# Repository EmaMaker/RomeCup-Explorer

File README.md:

# RomeCup Explorer

This repository contains the PCBs design files and code for the RomeCup Explorer playfield.

The RomeCup is a yearly event held by [Fondazione Mondo Digitale](https://mondodigitale.org) in
Rome, Italy, revolving around robotics and artificial intelligence. A big part of the event are the
robotics competitions aimed at middle and high school students. Some categories of competition are parallel to
the [RoboCup Junior](https://junior.robocup.org) (e.g. Soccer Open/LightWeight, Rescue Line), while
others are exclusive to RomeCup, like the Explorer category and, starting 2024, the Robotic Arms
category.

In the Explorer category, robots build and programmed by the students have to navigate a maze while
finding and recognizing different "hotspots". The hotspots can be of different kinds (in ascending
	order of points earned):

- Gas sources (1)
- Light source (2)
- Sound sources (3)

In 2024, we decided to rebuild the explorer category playfield from the ground up, favouring ease of
transport and assembly once on site (RomeCup is held every year at a different location, with the
	finals taking place in Rome Capitol every year).

To follow this route, we decided to have each hotspot have its own PCB to generate light and sound,
   instead of having a single source with cables running underneath the playfield. This also makes
   rearranging the maze easier in between rounds. In this repo, you can find the KiCad project files
   for the light and sound generation PCB, along side the BOM and manufacturing files for both
   standalone boards and panels, and the Arduino code powering the AtTiny412 microcontroller used in
   the sound boards. 

If you want to know more about the thought process and design decisions for the playfield, or about
the RoboCup 2024 event in general, I have written a [blog post](https://emamaker.com/events/romecup2024)
about it.

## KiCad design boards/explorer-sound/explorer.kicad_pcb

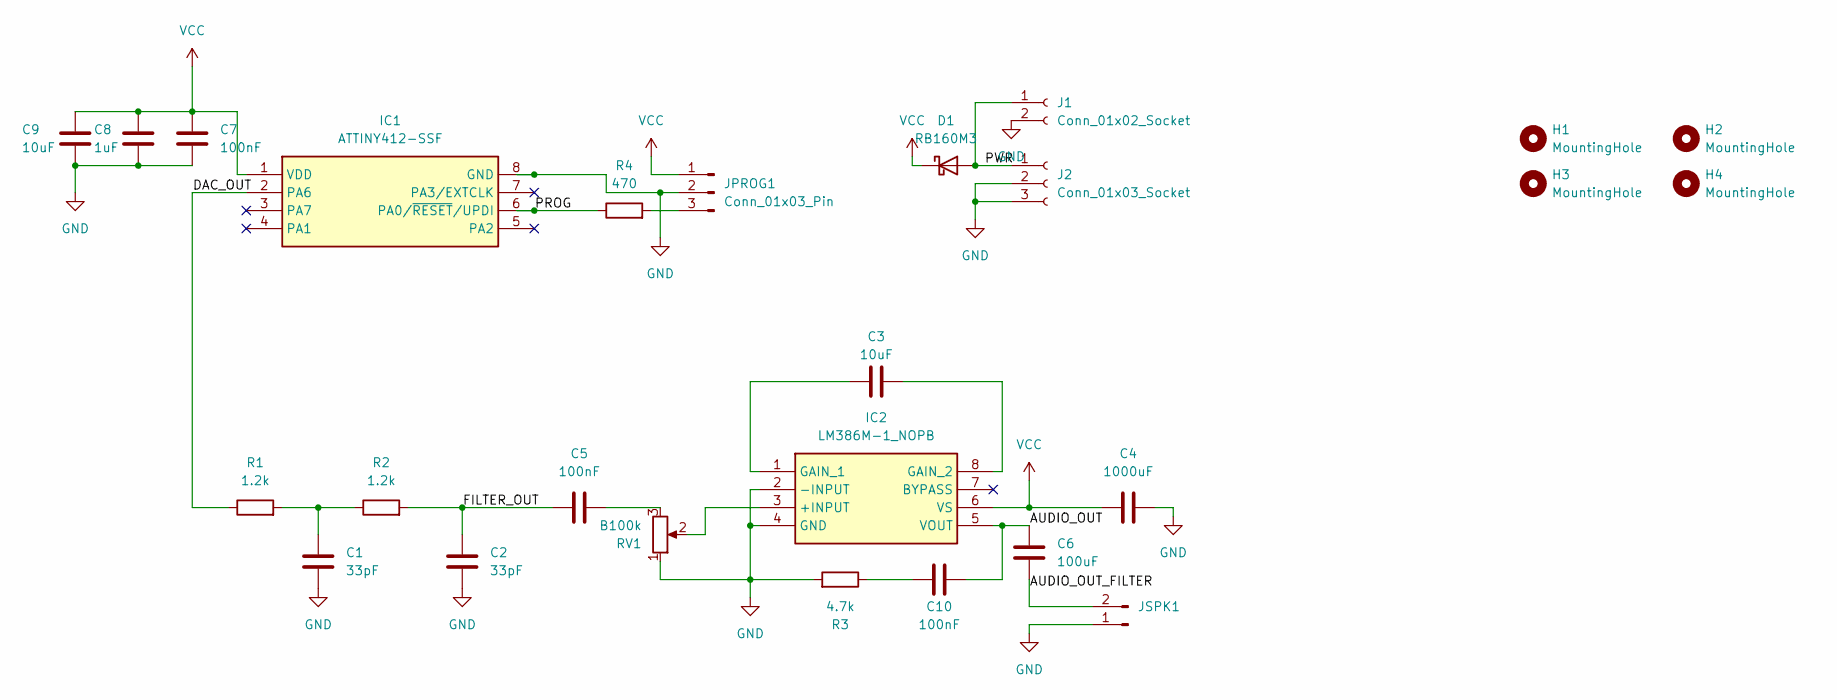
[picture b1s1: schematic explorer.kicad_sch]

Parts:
C1, C2: 33pF; C_0805_2012Metric_Pad1.18x1.45mm_HandSolder
C3, C9: 10uF; C_0805_2012Metric_Pad1.18x1.45mm_HandSolder
C4: 1000uF; CP_Elec_8x10.5
C5, C7, C10: 100nF; C_0805_2012Metric_Pad1.18x1.45mm_HandSolder
C6: 100uF; CP_Elec_8x10.5
C8: 1uF; C_0805_2012Metric_Pad1.18x1.45mm_HandSolder
D1: RB160M3; D_SOD-123
H1, H2, H3, H4: MountingHole; MountingHole_3.2mm_M3
IC1: ATTINY412-SSF; SOIC127P600X175-8N; Manufacturer_Part_Number ATTINY412-SSF; Mouser Part Number 579-ATTINY412-SSF
IC2: LM386M-1_NOPB; SOIC127P600X175-8N; Manufacturer_Part_Number LM386M-1/NOPB; Mouser Part Number 926-LM386M-1/NOPB
J1: Conn_01x02_Socket; TE_826576-2_1x02_P3.96mm_Vertical
J2: Conn_01x03_Socket; BarrelJack_Horizontal
JPROG1: Conn_01x03_Pin; PinHeader_1x03_P2.54mm_Vertical
JSPK1: Connector_PinHeader_2.54mm:PinHeader_1x02_P2.54mm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; PinHeader_1x02_P2.54mm_Vertical
R1, R2: 1.2k; R_0805_2012Metric_Pad1.20x1.40mm_HandSolder
R3: 4.7k; R_0805_2012Metric_Pad1.20x1.40mm_HandSolder
R4: 470; R_0805_2012Metric_Pad1.20x1.40mm_HandSolder
RV1: B100k; Potentiometer_Bourns_3214X_Vertical

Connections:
/AUDIO_OUT: C6.1, C10.2, IC2.5 (VOUT)
/AUDIO_OUT_FILTER: C6.2, JSPK1.2
/DAC_OUT: IC1.2 (PA6), R1.1
/FILTER_OUT: C2.1, C5.1, R2.2
/PROG: IC1.6 (PA0/~RESET/UPDI), R4.1
/PWR: D1.2 (A), J1.1, J2.1
GND: C1.2, C2.2, C4.2, C7.2, C8.2, C9.2, IC1.8 (GND), IC2.2 (-INPUT), IC2.4 (GND), J1.2, J2.2, J2.3, JPROG1.2, JSPK1.1, R3.2, RV1.1
unnamed: C1.1, R1.2, R2.1
unnamed: C5.2, RV1.3
unnamed: C10.1, R3.1
unnamed: IC2.3 (+INPUT), RV1.2
unnamed: C3.1, IC2.1 (GAIN_1)
unnamed: C3.2, IC2.8 (GAIN_2)
unnamed: JPROG1.3, R4.2
VCC: C4.1, C7.1, C8.1, C9.1, D1.1 (K), IC1.1 (VDD), IC2.6 (VS), JPROG1.1

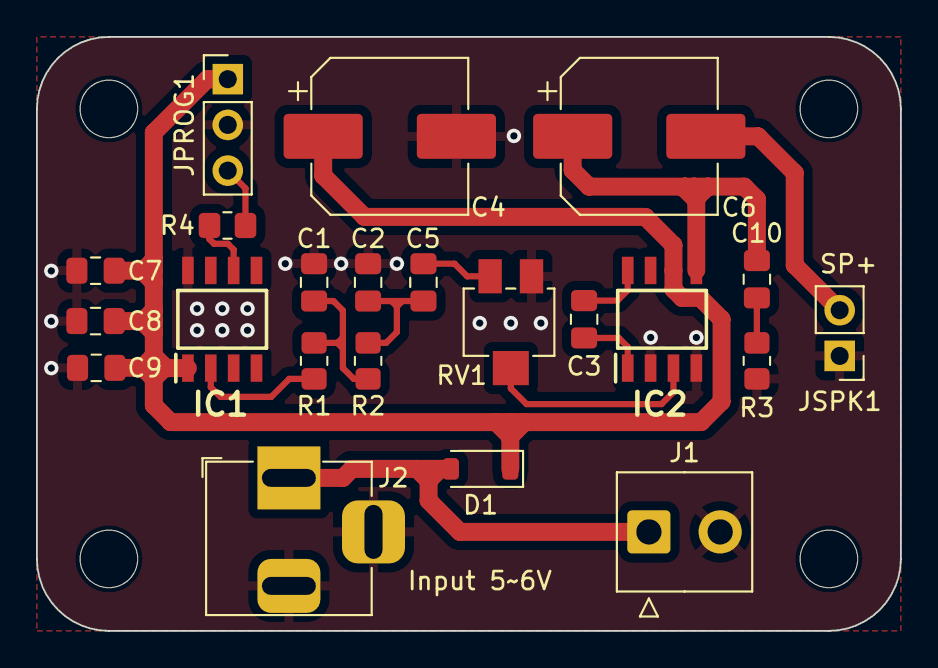
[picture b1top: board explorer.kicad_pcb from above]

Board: 2 copper layers, 48.0 x 33.0 mm, 26 parts (0 on the bottom side), 15 nets.

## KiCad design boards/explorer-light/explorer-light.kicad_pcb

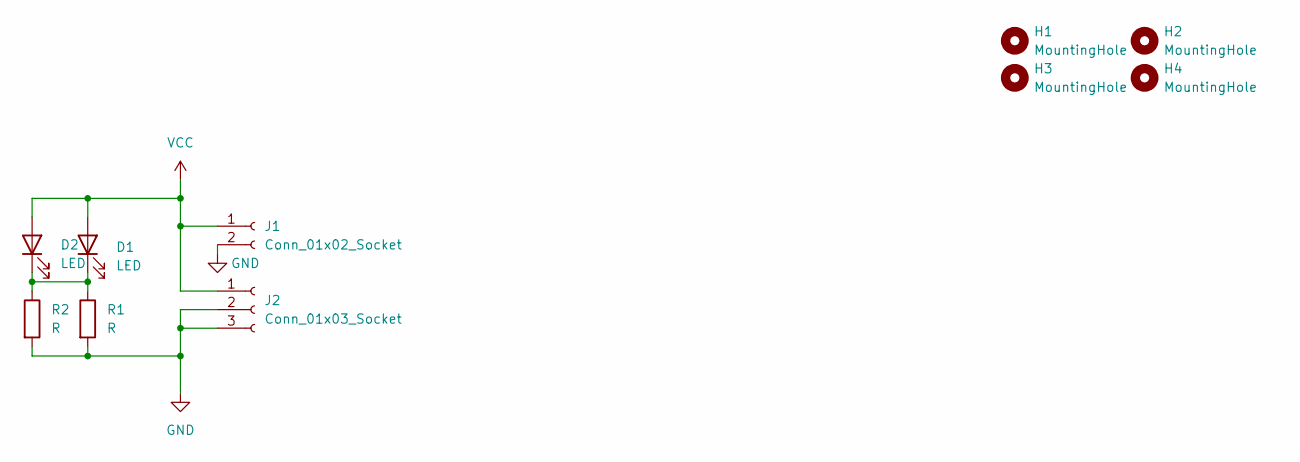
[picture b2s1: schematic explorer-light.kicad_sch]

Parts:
D1: LED; LED_2010_5025Metric_Pad1.52x2.65mm_HandSolder
D2: LED; LED_D5.0mm
H1, H2, H3, H4: MountingHole; MountingHole_3mm
J1: Conn_01x02_Socket; TE_826576-2_1x02_P3.96mm_Vertical
J2: Conn_01x03_Socket; BarrelJack_Horizontal
R1: R; R_Axial_DIN0309_L9.0mm_D3.2mm_P25.40mm_Horizontal
R2: R; R_0805_2012Metric_Pad1.20x1.40mm_HandSolder

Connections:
GND: J1.2, J2.2, J2.3, R1.2, R2.2
unnamed: D1.1 (K), D2.1 (K), R1.1, R2.1
VCC: D1.2 (A), D2.2 (A), J1.1, J2.1

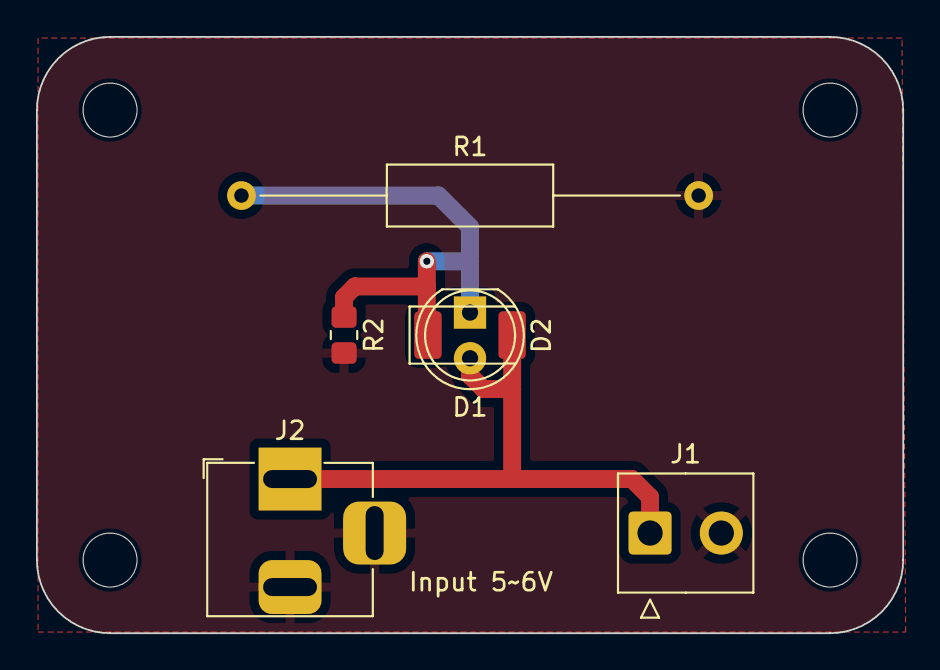
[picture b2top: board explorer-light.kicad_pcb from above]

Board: 2 copper layers, 48.1 x 33.1 mm, 10 parts (0 on the bottom side), 3 nets.

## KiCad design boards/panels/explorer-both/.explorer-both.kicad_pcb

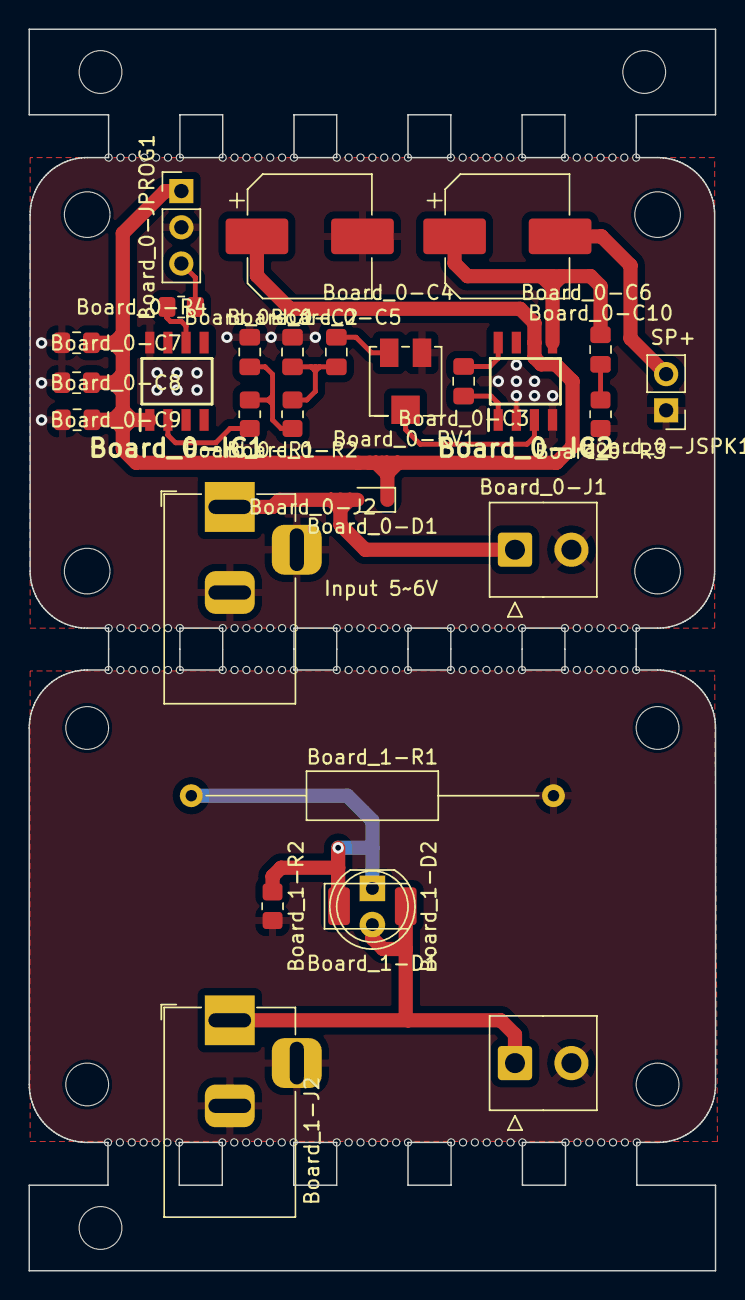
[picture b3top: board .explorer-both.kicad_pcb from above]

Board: 2 copper layers, 48.1 x 87.1 mm, 179 parts (0 on the bottom side), 18 nets.

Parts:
Board_0-C1, Board_0-C2: 33pF; C_0805_2012Metric_Pad1.18x1.45mm_HandSolder
Board_0-C3, Board_0-C9: 10uF; C_0805_2012Metric_Pad1.18x1.45mm_HandSolder
Board_0-C4: 1000uF; CP_Elec_8x10.5
Board_0-C5, Board_0-C7, Board_0-C10: 100nF; C_0805_2012Metric_Pad1.18x1.45mm_HandSolder
Board_0-C6: 100uF; CP_Elec_8x10.5
Board_0-C8: 1uF; C_0805_2012Metric_Pad1.18x1.45mm_HandSolder
Board_0-D1: D_Schottky; D_SOD-323
Board_0-H1, Board_0-H2, Board_0-H3, Board_0-H4: MountingHole; MountingHole_3.2mm_M3
Board_0-IC1: ATTINY412-SSF; SOIC127P600X175-8N
Board_0-IC2: LM386M-1_NOPB; SOIC127P600X175-8N
Board_0-J1, Board_1-J1: Conn_01x02_Socket; TE_826576-2_1x02_P3.96mm_Vertical
Board_0-J2, Board_1-J2: Conn_01x03_Socket; BarrelJack_Horizontal
Board_0-JPROG1: Conn_01x03_Pin; PinHeader_1x03_P2.54mm_Vertical
Board_0-JSPK1: Connector_PinHeader_2.54mm:PinHeader_1x02_P2.54mm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; PinHeader_1x02_P2.54mm_Vertical
Board_0-R1, Board_0-R2: 1.2k; R_0805_2012Metric_Pad1.20x1.40mm_HandSolder
Board_0-R3: 4.7k; R_0805_2012Metric_Pad1.20x1.40mm_HandSolder
Board_0-R4: 470; R_0805_2012Metric_Pad1.20x1.40mm_HandSolder
Board_0-RV1: B100k; Potentiometer_Bourns_3214J_Horizontal
Board_1-D1: LED; LED_2010_5025Metric_Pad1.52x2.65mm_HandSolder
Board_1-D2: LED; LED_D5.0mm
Board_1-H1, Board_1-H2, Board_1-H3, Board_1-H4: MountingHole; MountingHole_3mm
Board_1-R1: R; R_Axial_DIN0309_L9.0mm_D3.2mm_P25.40mm_Horizontal
Board_1-R2: R; R_0805_2012Metric_Pad1.20x1.40mm_HandSolder
KiKit_MB_1_1, KiKit_MB_1_2, KiKit_MB_1_3, KiKit_MB_1_4, KiKit_MB_1_5, KiKit_MB_1_6, KiKit_MB_1_7, KiKit_MB_2_1, KiKit_MB_2_2, KiKit_MB_2_3, KiKit_MB_2_4, KiKit_MB_2_5, KiKit_MB_2_6, KiKit_MB_2_7, KiKit_MB_3_1, KiKit_MB_3_2, KiKit_MB_3_3, KiKit_MB_3_4, KiKit_MB_3_5, KiKit_MB_3_6, KiKit_MB_3_7, KiKit_MB_4_1, KiKit_MB_4_2, KiKit_MB_4_3, KiKit_MB_4_4, KiKit_MB_4_5, KiKit_MB_4_6, KiKit_MB_4_7, KiKit_MB_5_1, KiKit_MB_5_2, KiKit_MB_5_3, KiKit_MB_5_4, KiKit_MB_5_5, KiKit_MB_5_6, KiKit_MB_5_7, KiKit_MB_6_1, KiKit_MB_6_2, KiKit_MB_6_3, KiKit_MB_6_4, KiKit_MB_6_5, KiKit_MB_6_6, KiKit_MB_6_7, KiKit_MB_7_1, KiKit_MB_7_2, KiKit_MB_7_3, KiKit_MB_7_4, KiKit_MB_7_5, KiKit_MB_7_6, KiKit_MB_7_7, KiKit_MB_8_1, KiKit_MB_8_2, KiKit_MB_8_3, KiKit_MB_8_4, KiKit_MB_8_5, KiKit_MB_8_6, KiKit_MB_8_7, KiKit_MB_9_1, KiKit_MB_9_2, KiKit_MB_9_3, KiKit_MB_9_4, KiKit_MB_9_5, KiKit_MB_9_6, KiKit_MB_9_7, KiKit_MB_10_1, KiKit_MB_10_2, KiKit_MB_10_3, KiKit_MB_10_4, KiKit_MB_10_5, KiKit_MB_10_6, KiKit_MB_10_7, KiKit_MB_11_1, KiKit_MB_11_2, KiKit_MB_11_3, KiKit_MB_11_4, KiKit_MB_11_5, KiKit_MB_11_6, KiKit_MB_11_7, KiKit_MB_12_1, KiKit_MB_12_2, KiKit_MB_12_3, KiKit_MB_12_4, KiKit_MB_12_5, KiKit_MB_12_6, KiKit_MB_12_7, KiKit_MB_13_1, KiKit_MB_13_2, KiKit_MB_13_3, KiKit_MB_13_4, KiKit_MB_13_5, KiKit_MB_13_6, KiKit_MB_13_7, KiKit_MB_14_1, KiKit_MB_14_2, KiKit_MB_14_3, KiKit_MB_14_4, KiKit_MB_14_5, KiKit_MB_14_6, KiKit_MB_14_7, KiKit_MB_15_1, KiKit_MB_15_2, KiKit_MB_15_3, KiKit_MB_15_4, KiKit_MB_15_5, KiKit_MB_15_6, KiKit_MB_15_7, KiKit_MB_16_1, KiKit_MB_16_2, KiKit_MB_16_3, KiKit_MB_16_4, KiKit_MB_16_5, KiKit_MB_16_6, KiKit_MB_16_7, KiKit_MB_17_1, KiKit_MB_17_2, KiKit_MB_17_3, KiKit_MB_17_4, KiKit_MB_17_5, KiKit_MB_17_6, KiKit_MB_17_7, KiKit_MB_18_1, KiKit_MB_18_2, KiKit_MB_18_3, KiKit_MB_18_4, KiKit_MB_18_5, KiKit_MB_18_6, KiKit_MB_18_7, KiKit_MB_19_1, KiKit_MB_19_2, KiKit_MB_19_3, KiKit_MB_19_4, KiKit_MB_19_5, KiKit_MB_19_6, KiKit_MB_19_7, KiKit_MB_20_1, KiKit_MB_20_2, KiKit_MB_20_3, KiKit_MB_20_4, KiKit_MB_20_5, KiKit_MB_20_6, KiKit_MB_20_7: NPTH
KiKit_TO_1, KiKit_TO_2, KiKit_TO_3: NPTH

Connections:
Board_0-/AUDIO_OUT: Board_0-C6.1, Board_0-C10.2, Board_0-IC2.5 (VOUT)
Board_0-/AUDIO_OUT_FILTER: Board_0-C6.2, Board_0-JSPK1.2
Board_0-/DAC_OUT: Board_0-IC1.2 (PA6), Board_0-R1.1
Board_0-/FILTER_OUT: Board_0-C2.1, Board_0-C5.1, Board_0-R2.2
Board_0-/PROG: Board_0-IC1.6 (PA0/~RESET/UPDI), Board_0-R4.1
Board_0-/PWR: Board_0-D1.2 (A), Board_0-J1.1, Board_0-J2.1
Board_0-GND: Board_0-C1.2, Board_0-C2.2, Board_0-C4.2, Board_0-C7.2, Board_0-C8.2, Board_0-C9.2, Board_0-IC1.8 (GND), Board_0-IC2.2 (-INPUT), Board_0-IC2.4 (GND), Board_0-J1.2, Board_0-J2.2, Board_0-J2.3, Board_0-JPROG1.2, Board_0-JSPK1.1, Board_0-R3.2, Board_0-RV1.3
Board_0-Net-(C1-Pad1): Board_0-C1.1, Board_0-R1.2, Board_0-R2.1
Board_0-Net-(C5-Pad2): Board_0-C5.2, Board_0-RV1.1
Board_0-Net-(C10-Pad1): Board_0-C10.1, Board_0-R3.1
Board_0-Net-(IC2-+INPUT): Board_0-IC2.3 (+INPUT), Board_0-RV1.2
Board_0-Net-(IC2-GAIN_1): Board_0-C3.1, Board_0-IC2.1 (GAIN_1)
Board_0-Net-(IC2-GAIN_2): Board_0-C3.2, Board_0-IC2.8 (GAIN_2)
Board_0-Net-(JPROG1-Pin_3): Board_0-JPROG1.3, Board_0-R4.2
Board_0-VCC: Board_0-C4.1, Board_0-C7.1, Board_0-C8.1, Board_0-C9.1, Board_0-D1.1 (K), Board_0-IC1.1 (VDD), Board_0-IC2.6 (VS), Board_0-JPROG1.1
Board_1-GND: Board_1-J1.2, Board_1-J2.2, Board_1-J2.3, Board_1-R1.2, Board_1-R2.2
Board_1-Net-(D1-K): Board_1-D1.1 (K), Board_1-D2.1 (K), Board_1-R1.1, Board_1-R2.1
Board_1-VCC: Board_1-D1.2 (A), Board_1-D2.2 (A), Board_1-J1.1, Board_1-J2.1

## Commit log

2024-03-23 add REAME.md
2024-03-23 add light station pcb project+gerber
2024-03-23 add sound station pcb project+gerber
2024-03-23 add projects for panels
2024-03-23 add code for sound board. Use attiny-sound-32bit-final
